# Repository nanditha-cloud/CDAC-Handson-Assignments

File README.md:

I have added all the assignments week wise and converted to rar format. In outputs folder, along with gerber files I added few output screenshots in the same folder and also eagle board and schematic files.

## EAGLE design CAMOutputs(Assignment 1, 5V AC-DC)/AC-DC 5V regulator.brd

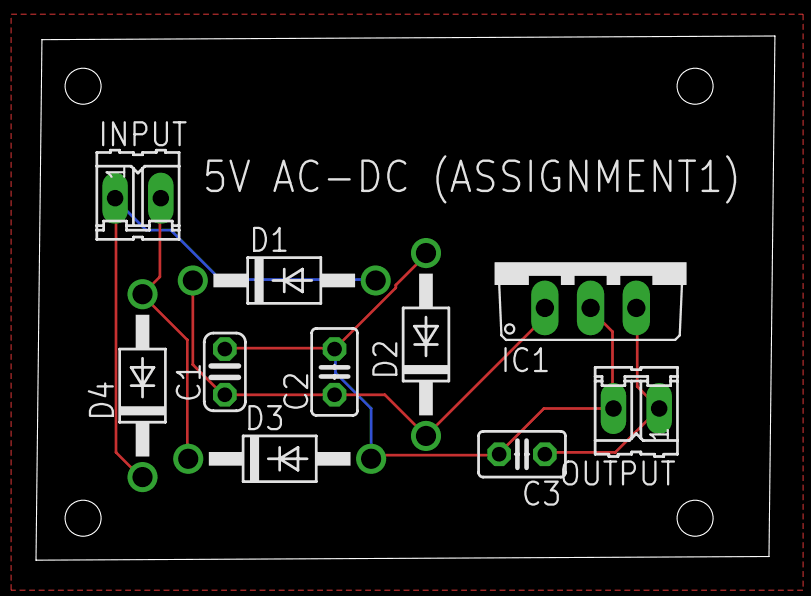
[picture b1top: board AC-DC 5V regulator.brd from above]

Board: 2 copper layers, 41.1 x 29.1 mm, 10 parts (0 on the bottom side), 5 nets.

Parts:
C1: 1000uF; C025-024X044
C2, C3: 0.1uF; C025-025X050
D1, D2, D3, D4: 1N4007; DO41-10
IC1: LM7805; TO220V
INPUT: 02P
OUTPUT: 02P

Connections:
GND: C1.2, C2.2, C3.2, D2.A, D3.A, IC1.2, OUTPUT.2
unnamed: D1.A, D4.C, INPUT.1
unnamed: D3.C, D4.A, INPUT.2
unnamed: C1.1, C2.1, D1.C, D2.C, IC1.1
unnamed: C3.1, IC1.3, OUTPUT.1

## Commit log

2021-04-27 Create Week1
